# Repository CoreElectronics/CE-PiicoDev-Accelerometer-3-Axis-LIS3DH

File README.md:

# PiicoDev® Acceleromter LIS3DH

This is the repo for the Core Electronics [PiicoDev Accelerometer LIS3DH](https://core-electronics.com.au/catalog/product/view/sku/CE08705).

## License
This project is open source - please review the LICENSE.md file for further licensing information.

If you have any technical questions, or concerns about licensing, please contact technical support on the [Core Electronics forums](https://forum.core-electronics.com.au/).

*\"PiicoDev\" and the PiicoDev logo are trademarks of Core Electronics Pty Ltd.*

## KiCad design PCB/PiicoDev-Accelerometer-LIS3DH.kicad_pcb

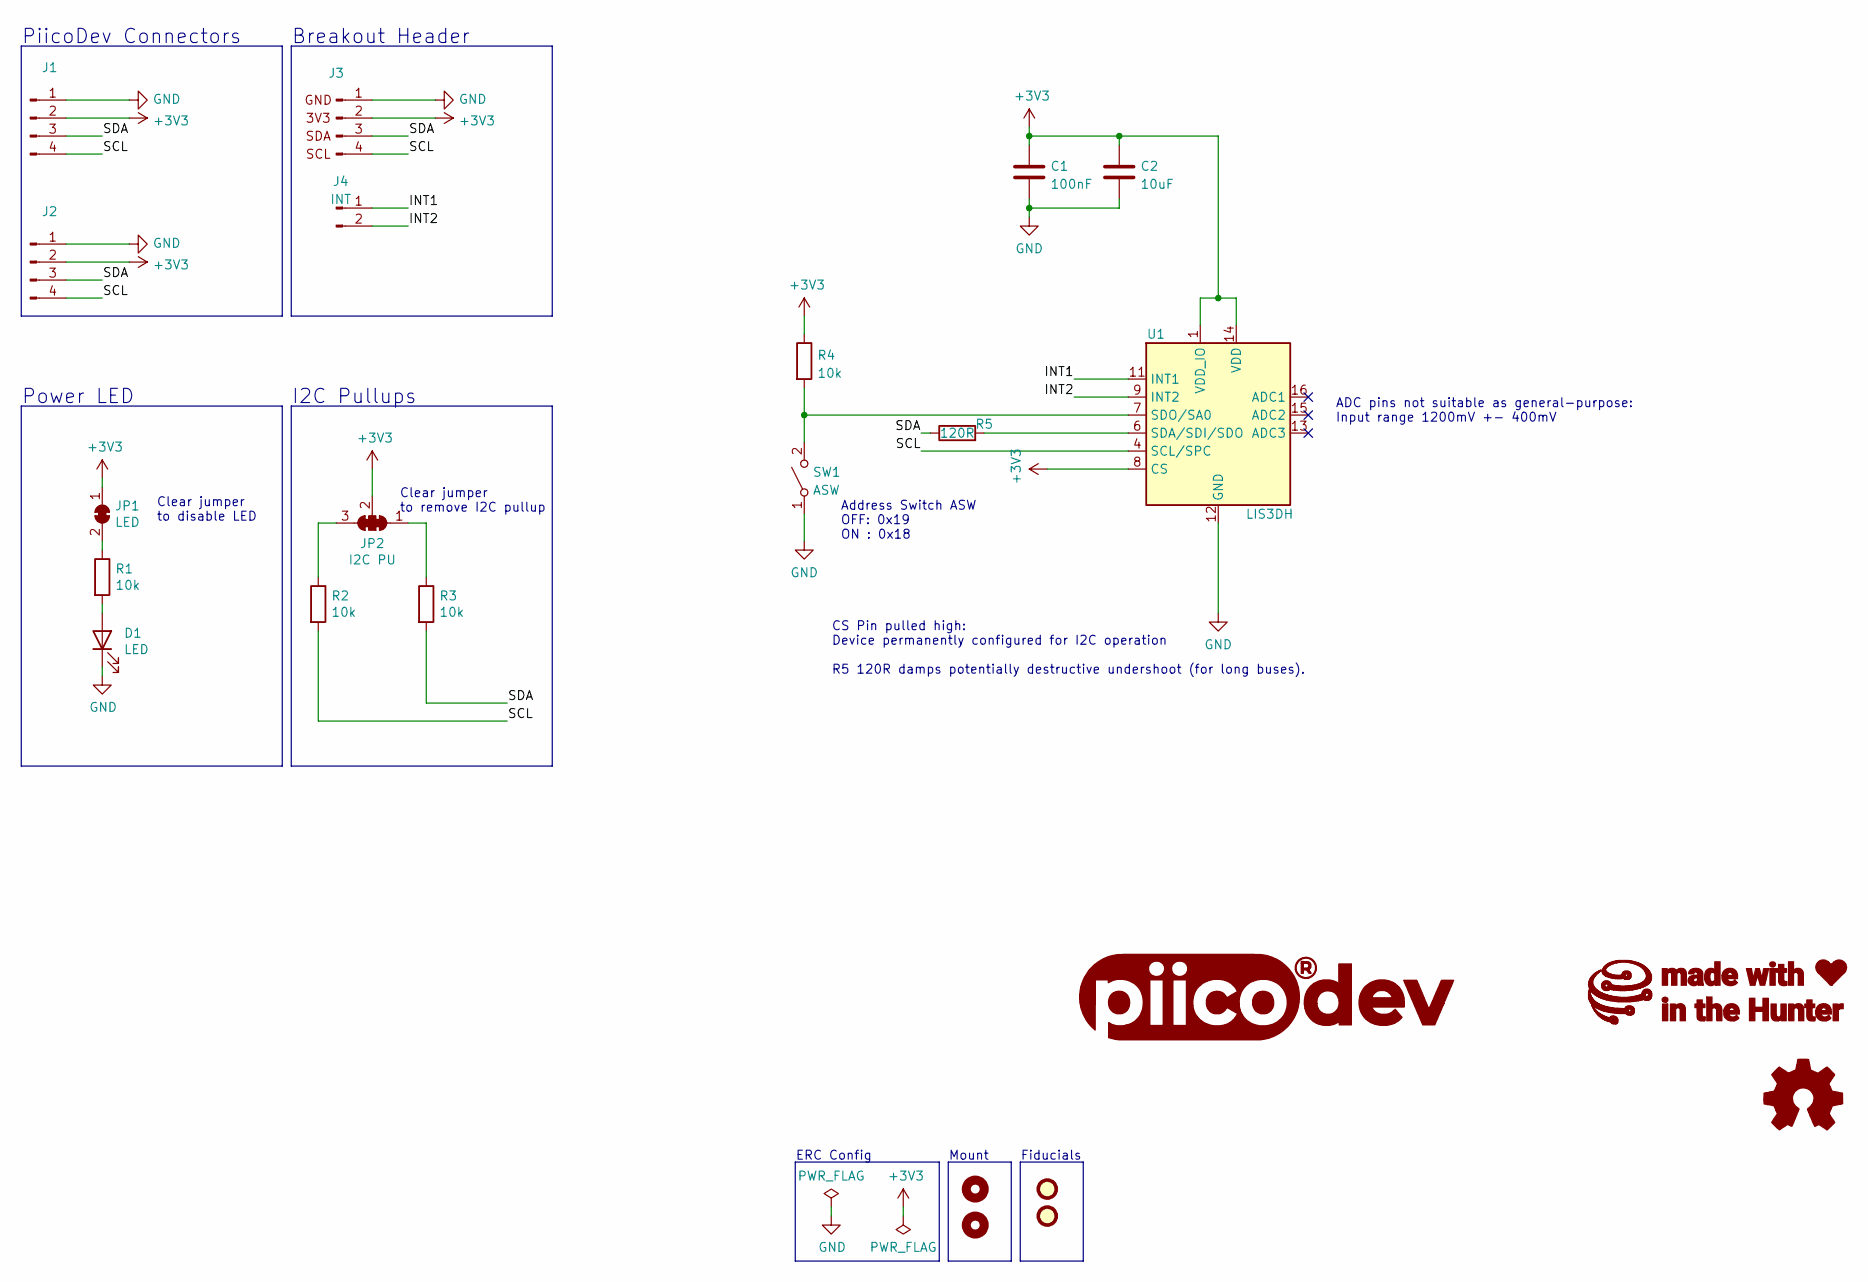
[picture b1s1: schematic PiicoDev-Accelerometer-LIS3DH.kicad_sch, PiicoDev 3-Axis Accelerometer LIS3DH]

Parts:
C1: 100nF; C_0402_1005Metric
C2: 10uF; C_0603_1608Metric
D1: LED; LED_0603_1608Metric
FID1, FID2: Fiducial; Fiducial_1mm_Mask2mm
G1: LOGO_PiicoDev; piicodev_logo_14.2x3.4mm
G2: LOGO_CoreElectronics_no-text; CoreElectronics_logo_5mm
G3: LOGO_made-with-love; piicodev_logo_14.2x3.4mm
H1, H2: MountingHole; MountingHole_2.7mm_M2.5_PadClearance_1.2
J1, J2: JST_SH_SM04B-SRSS-TB_1x04-1MP_P1.00mm_Horizontal
J3: Conn_PiicoDev_header_01x04_Male; PiicoDev_header_4pin
J4: INT; PinHeader_1x02_P2.54mm_Vertical
JP1: LED; SolderJumper-2_P1.3mm_Bridged_RoundedPad1.0x1.5mm
JP2: I2C PU; SolderJumper-3_P1.3mm_Closed_RoundedPad1.0x1.5mm_NumberLabe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
LOGO1: Logo_Open_Hardware_Small; oshw
R1, R2, R3, R4: 10k; R_0402_1005Metric
R5: 120R; R_0402_1005Metric
SW1: ASW; SW_DIP_x01_Slide_CHS-01A1
U1: LIS3DH; LGA-16_3x3mm_P0.5mm_LayoutBorder3x5y

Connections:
+3V3: C1.1, C2.1, J1.2, J2.2, J3.2, JP1.1 (A), JP2.2 (C), R4.1, U1.1 (VDD_IO), U1.8 (CS), U1.14 (VDD)
/INT1: J4.1, U1.11 (INT1)
/INT2: J4.2, U1.9 (INT2)
/SCL: J1.4, J2.4, J3.4, R2.2, U1.4 (SCL/SPC)
/SDA: J1.3, J2.3, J3.3, R3.2, R5.1
GND: C1.2, C2.2, D1.1 (K), J1.1, J2.1, J3.1, SW1.1 (A), U1.5 (GND), U1.10 (GND), U1.12 (GND)
unnamed: D1.2 (A), R1.2
unnamed: JP1.2 (B), R1.1
unnamed: JP2.1 (A), R3.1
unnamed: JP2.3 (B), R2.1
unnamed: R4.2, SW1.2 (B), U1.7 (SDO/SA0)
unnamed: R5.2, U1.6 (SDA/SDI/SDO)

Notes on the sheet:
Breakout Header
Address Switch ASW OFF: 0x19 ON : 0x18
Fiducials
I2C Pullups
CS Pin pulled high: Device permanently configured for I2C operation R5 120R damps potentially destructive undershoot (for long buses).
Clear jumper to remove I2C pullup
ERC Config
ADC pins not suitable as general-purpose: Input range 1200mV +- 400mV
Power LED
Clear jumper to disable LED
Mount
PiicoDev Connectors

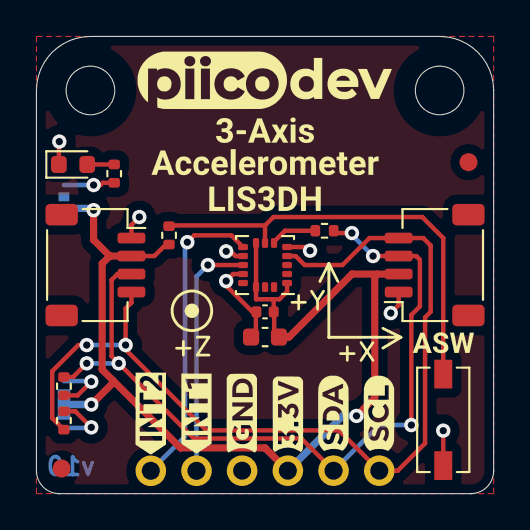
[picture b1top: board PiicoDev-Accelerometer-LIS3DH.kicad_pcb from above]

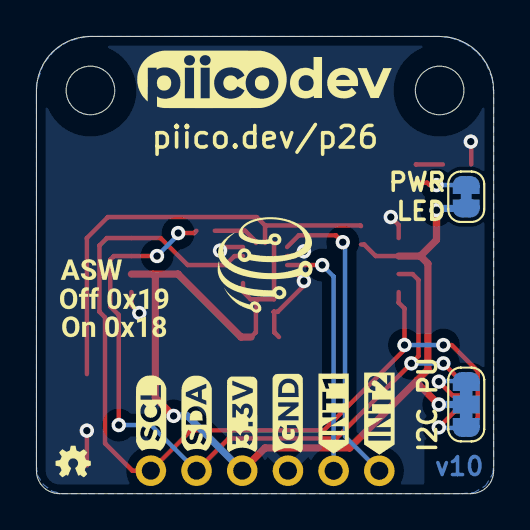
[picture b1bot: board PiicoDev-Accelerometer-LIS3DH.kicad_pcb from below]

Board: 2 copper layers, 25.4 x 25.4 mm, 38 parts (11 on the bottom side), 12 nets.

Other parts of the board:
Ref**: Axes_and_polarity_Y
Ref**#2: Axes_and_polarity_Z
Ref**#3: Axes_and_polarity_X
kibuzzard-62B3F7CF: G***; kibuzzard-62B3F7CF
kibuzzard-62B3F7FD: G***; kibuzzard-62B3F7FD
kibuzzard-62B3F9C2, kibuzzard-62B3F9C2#2: G***; kibuzzard-62B3F9C2
kibuzzard-62B3F9DB, kibuzzard-62B3F9DB#2: G***; kibuzzard-62B3F9DB
kibuzzard-62B3F80B: G***; kibuzzard-62B3F80B
kibuzzard-62B3F81B: G***; kibuzzard-62B3F81B
kibuzzard-62B4082B: G***; kibuzzard-62B4082B
kibuzzard-62B4083B: G***; kibuzzard-62B4083B
kibuzzard-62B40846: G***; kibuzzard-62B40846

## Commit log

2022-06-23 Initial Commit v00 prototype
2022-07-21 add documents and link CAD
2022-08-11 add schematic.pdf
2022-08-12 add image

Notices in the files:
PCB/PiicoDev-Accelerometer-LIS3DH.kicad_sch:
License: CCASAv4.0 http://creativecommons.org/licenses/by-sa/4.0
